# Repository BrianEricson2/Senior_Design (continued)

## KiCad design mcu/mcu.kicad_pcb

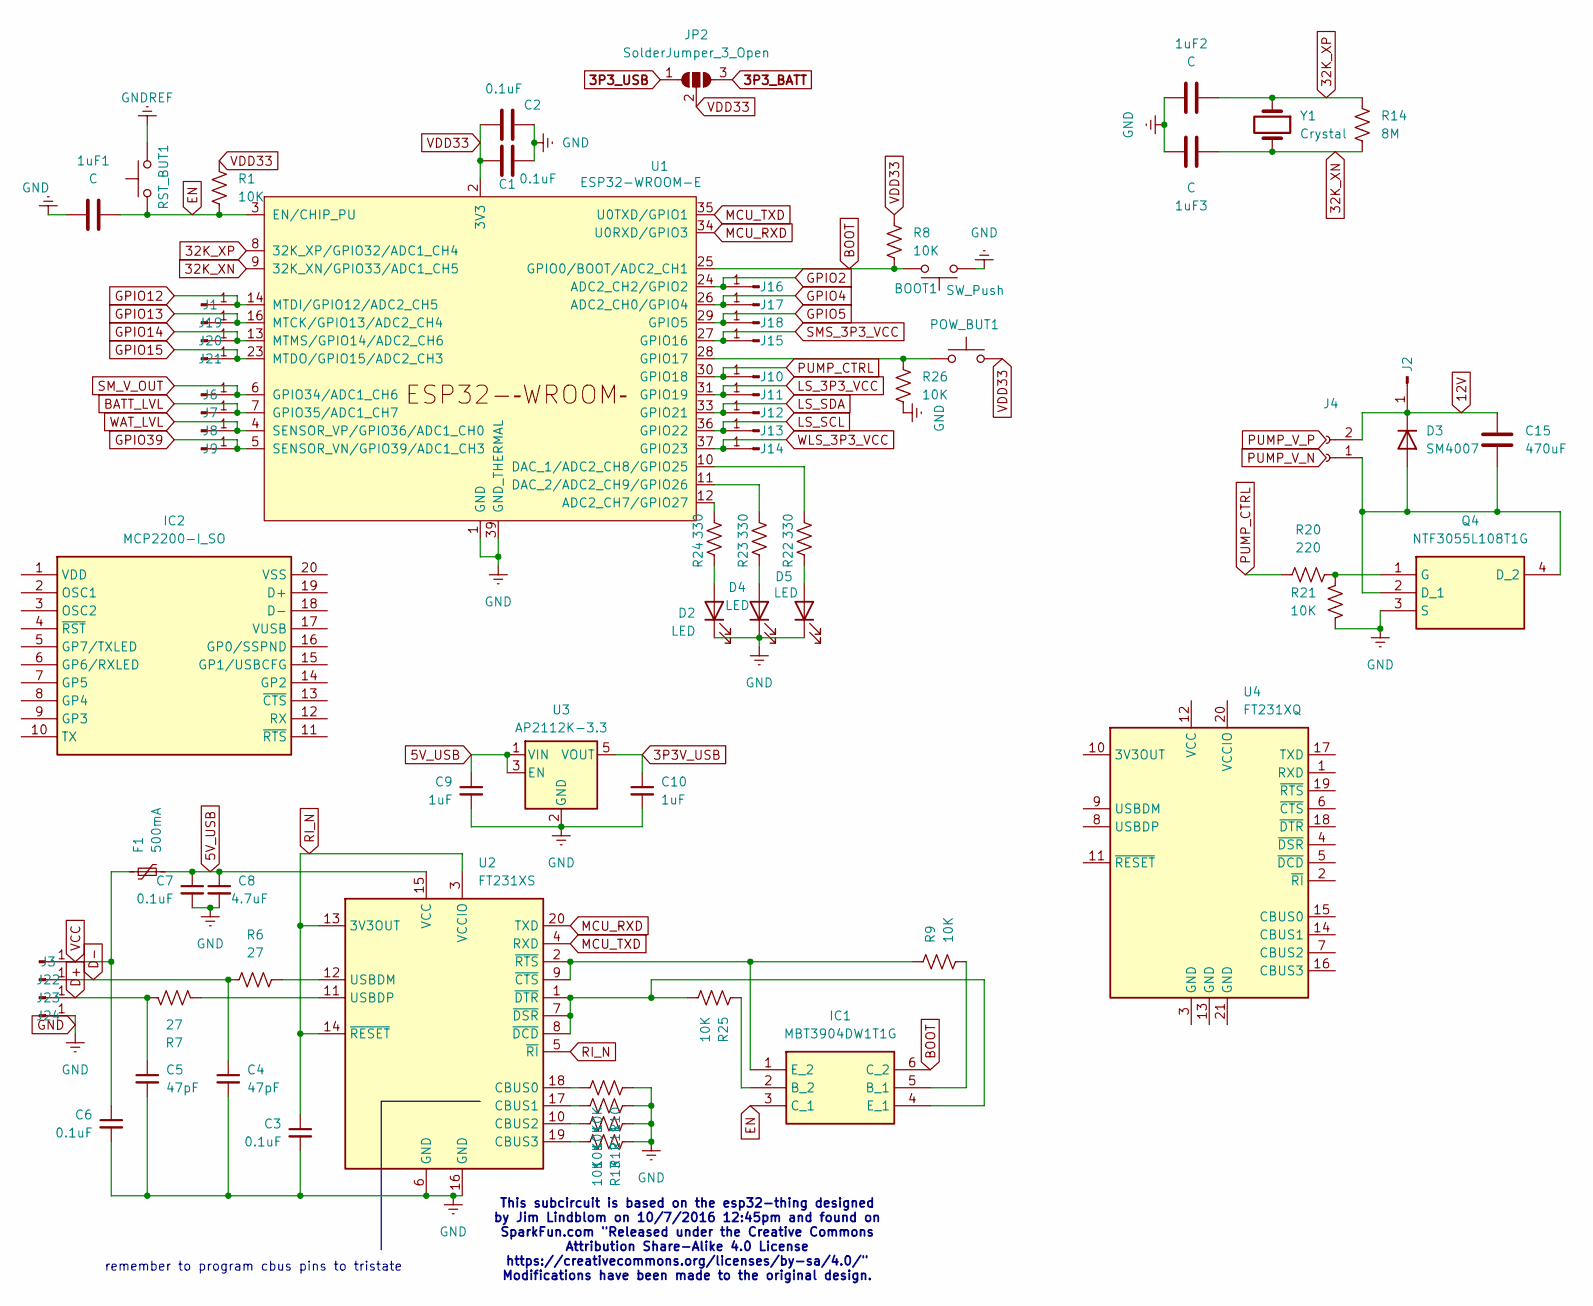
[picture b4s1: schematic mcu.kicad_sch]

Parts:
1uF1, 1uF2, 1uF3: C; C_1206_3216Metric_Pad1.33x1.80mm_HandSolder
BOOT1: SW_Push; SW_Push_SPST_NO_Alps_SKRK
C1, C2, C3, C6, C7: 0.1uF; C_1206_3216Metric_Pad1.33x1.80mm_HandSolder
C4, C5: 47pF; C_1206_3216Metric_Pad1.33x1.80mm_HandSolder
C8: 4.7uF; C_1206_3216Metric_Pad1.33x1.80mm_HandSolder
C9, C10: 1uF; C_1206_3216Metric_Pad1.33x1.80mm_HandSolder
C15: 470uF; C_1206_3216Metric_Pad1.33x1.80mm_HandSolder
D2, D4, D5: LED; LED_1206_3216Metric_Pad1.42x1.75mm_HandSolder
D3: SM4007; D_MELF
F1: 500mA; Fuse_1206_3216Metric_Pad1.42x1.75mm_HandSolder
IC1: MBT3904DW1T1G; SOT65P210X110-6N; Mouser Part Number 863-MBT3904DW1T1G
IC2: MCP2200-I_SO; SOIC127P1030X265-20N; Mouser Part Number 579-MCP2200-I/SO
J1, J2, J3, J6, J7, J8, J9, J10, J11, J12, J13, J14, J15, J16, J17, J18, J19, J20, J21, J22, J23, J24: Conn_01x01_Pin; PinHeader_1x01_P2.00mm_Vertical
J4: Conn_01x02; PinSocket_1x02_P1.00mm_Vertical_SMD_Pin1Left
JP2: SolderJumper_3_Open; SolderJumper-3_P1.3mm_Open_Pad1.0x1.5mm_NumberLabels
POW_BUT1: SW_Push; SW_Push_SPST_NO_Alps_SKRK
Q4: NTF3055L108T1G; SOT230P700X175-4N; Mouser Part Number 863-NTF3055L108T1G
R1, R8, R9, R10, R11, R12, R13, R21, R25, R26: 10K; R_1206_3216Metric_Pad1.30x1.75mm_HandSolder
R6, R7: 27; R_1206_3216Metric_Pad1.30x1.75mm_HandSolder
R14: 8M; R_1206_3216Metric_Pad1.30x1.75mm_HandSolder
R20: 220; R_1206_3216Metric_Pad1.30x1.75mm_HandSolder
R22, R23, R24: 330; R_1206_3216Metric_Pad1.30x1.75mm_HandSolder
RST_BUT1: SW_Push; SW_Push_SPST_NO_Alps_SKRK
U1: ESP32-WROOM-E; ESP32-WROOM-32E
U2: FT231XS; SSOP-20_3.9x8.7mm_P0.635mm
U3: AP2112K-3.3; SOT-23-5
U4: FT231XQ; QFN-20-1EP_4x4mm_P0.5mm_EP2.5x2.5mm
Y1: Crystal; Crystal_SMD_TXC_AX_8045-2Pin_8.0x4.5mm

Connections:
3P3V_USB: C10.1, U3.5 (VOUT)
3P3_BATT: JP2.3 (B)
3P3_USB: JP2.1 (A)
5V_USB: C7.1, C8.1, C9.1, F1.2, U2.15 (VCC), U3.1 (VIN), U3.3 (EN)
12V: C15.1, D3.1 (K), J2.1, J4.2
32K_XN: 1uF3.1, R14.2, U1.9 (32K_XN/GPIO33/ADC1_CH5), Y1.2
32K_XP: 1uF2.1, R14.1, U1.8 (32K_XP/GPIO32/ADC1_CH4), Y1.1
BATT_LVL: J7.1, U1.7 (GPIO35/ADC1_CH7)
BOOT: BOOT1.1, IC1.6 (C_2), R8.2, U1.25 (GPIO0/BOOT/ADC2_CH1)
D+: C5.1, J23.1, R7.2
D-: C4.1, J22.1, R6.2
EN: 1uF1.1, IC1.3 (C_1), R1.2, RST_BUT1.1, U1.3 (EN/CHIP_PU)
GND: 1uF1.2, 1uF2.2, 1uF3.2, BOOT1.2, C1.1, C2.1, C3.2, C4.2, C5.2, C6.2, C7.2, C8.2, C9.2, C10.2, D2.1 (K), D4.1 (K), D5.1 (K), J24.1, Q4.3 (S), R10.1, R11.1, R12.1, R13.1, R21.2, R26.2, U1.1 (GND), U1.15 (GND), U1.38 (GND), U1.39 (GND_THERMAL), U2.6 (GND), U2.16 (GND), U3.2 (GND)
GNDREF: RST_BUT1.2
GPIO2: J16.1, U1.24 (ADC2_CH2/GPIO2)
GPIO4: J17.1, U1.26 (ADC2_CH0/GPIO4)
GPIO5: J18.1, U1.29 (GPIO5)
GPIO12: J1.1, U1.14 (MTDI/GPIO12/ADC2_CH5)
GPIO13: J19.1, U1.16 (MTCK/GPIO13/ADC2_CH4)
GPIO14: J20.1, U1.13 (MTMS/GPIO14/ADC2_CH6)
GPIO15: J21.1, U1.23 (MTDO/GPIO15/ADC2_CH3)
GPIO39: J9.1, U1.5 (SENSOR_VN/GPIO39/ADC1_CH3)
LS_3P3_VCC: J11.1, U1.31 (GPIO19)
LS_SCL: J13.1, U1.36 (GPIO22)
LS_SDA: J12.1, U1.33 (GPIO21)
MCU_RXD: U1.34 (U0RXD/GPIO3), U2.20 (TXD)
MCU_TXD: U1.35 (U0TXD/GPIO1), U2.4 (RXD)
unnamed: D2.2 (A), R24.1
unnamed: C15.2, D3.2 (A), J4.1, Q4.2 (D_1), Q4.4 (D_2)
unnamed: D4.2 (A), R23.1
unnamed: D5.2 (A), R22.1
unnamed: IC1.5 (B_1), R9.2
unnamed: IC1.2 (B_2), R25.1
unnamed: IC1.4 (E_1), R25.2, U2.1 (~DTR), U2.7 (~DSR), U2.8 (~DCD)
unnamed: IC1.1 (E_2), R9.1, U2.2 (~RTS), U2.9 (~CTS)
unnamed: Q4.1 (G), R20.2, R21.1
unnamed: R24.2, U1.12 (ADC2_CH7/GPIO27)
unnamed: R22.2, U1.10 (DAC_1/ADC2_CH8/GPIO25)
unnamed: R23.2, U1.11 (DAC_2/ADC2_CH9/GPIO26)
unnamed: POW_BUT1.2, R26.1, U1.28 (GPIO17)
unnamed: R10.2, U2.18 (CBUS0)
unnamed: R11.2, U2.17 (CBUS1)
unnamed: R12.2, U2.10 (CBUS2)
unnamed: R13.2, U2.19 (CBUS3)
unnamed: R6.1, U2.12 (USBDM)
unnamed: R7.1, U2.11 (USBDP)
PUMP_CTRL: J10.1, R20.1, U1.30 (GPIO18)
RI_N: C3.1, U2.3 (VCCIO), U2.5 (~RI), U2.13 (3V3OUT), U2.14 (~RESET)
SMS_3P3_VCC: J15.1, U1.27 (GPIO16)
SM_V_OUT: J6.1, U1.6 (GPIO34/ADC1_CH6)
VCC: C6.1, F1.1, J3.1
VDD33: C1.2, C2.2, JP2.2 (C), POW_BUT1.1, R1.1, R8.1, U1.2 (3V3)
WAT_LVL: J8.1, U1.4 (SENSOR_VP/GPIO36/ADC1_CH0)
WLS_3P3_VCC: J14.1, U1.37 (GPIO23)

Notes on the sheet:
This subcircuit is based on the esp32-thing designed by Jim Lindblom on 10/7/2016 12:45pm and found on SparkFun.com "Released under the Creative Commons Attribution Share-Alike 4.0 License https://creativecommons.org/licenses/by-sa/4.0/" Modifications have been made to the original design.
remember to program cbus pins to tristate

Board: 4 copper layers, 71 parts (0 on the bottom side), 51 nets, no tracks yet.

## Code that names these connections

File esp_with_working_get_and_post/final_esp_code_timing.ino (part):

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String sampling_period_disp = "";
String watering_duration_disp = "";

const int water_lvl_pin = 36; //GPIO36 - pin 4
const int sms_data_pin = 34; //GPIO34 - pin 6
const int battery_lvl_pin = 35; //GPIO35 - pin 7
const int sms_power_pin = 16; //GPIO16 - pin 27
const int light_sensor_pwr_pin = 17; //GPIO17 - pin 28
const int pump_ctrl_pin = 18; //GPIO18 - pin 30
const int wls_power_pin = 23; //GPIO23 - pin 37
const int ledPin     = 2;    // Onboard blue LED

// use addr 0x23 if addr pin voltage is < 0.7*Vcc
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
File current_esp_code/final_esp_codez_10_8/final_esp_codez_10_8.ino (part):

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// String sampling_period_disp = "";
// String watering_duration_disp = "";

const int light_sensor_pwr_pin = 18; //GPIO18
const int pump_ctrl_pin = 16; //GPIO16
const int sms_power_pin = 19; //GPIO19
const int i2c_sda = 21; // i2c serial data = GPIO 21
const int i2c_scl = 22; // i2c serial clock = GPIO22
const int wls_power_pin = 23; //GPIO23
const int ledPin1     = 25; // pin 10 on esp32 ic
const int ledPin2     = 26; // pin 11 on esp32 ic
const int ledPin3     = 27; // pin 12 on esp32 ic
const int sms_data_pin = 32; //GPIO32
const int battery_lvl_pin = 34; //GPIO34
const int wls_signal = 35;

// use addr 0x23 if addr pin voltage is < 0.7*Vcc
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  pinMode(ledPin2, OUTPUT); digitalWrite(ledPin2, LOW);
  pinMode(ledPin3, OUTPUT); digitalWrite(ledPin3, LOW);
  //digitalWrite(wls_power_pin,LOW);
  pinMode(pump_ctrl_pin,OUTPUT); digitalWrite(pump_ctrl_pin,LOW);
  pinMode(sms_power_pin,OUTPUT); digitalWrite(sms_power_pin,LOW);
  pinMode(light_sensor_pwr_pin,OUTPUT); digitalWrite(light_sensor_pwr_pin,LOW);
  pinMode(wls_power_pin,OUTPUT); digitalWrite(wls_power_pin,LOW);
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void water_plant() {
  Serial.println("Enabling power to plant");
  unsigned long current_time = micros();
  digitalWrite(pump_ctrl_pin, HIGH);
  digitalWrite(ledPin3, HIGH);

  // (max limit - buffer) - current_time
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    unsigned long stop_counter = watering_duration_us - dist_from_limit;
    while(micros() < stop_counter) {}
  }
  digitalWrite(pump_ctrl_pin, LOW);
  digitalWrite(ledPin3, LOW);
  
  Serial.println("Disabling power to plant");
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
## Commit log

2025-06-22 Async Web Server; Est. Wifi connection
2025-07-08 Initialize soil moisture sensor data; sleep mode; timer wakeup; can not display web page while using sleep mode
2025-07-09 Create Demo
2025-07-21 peripheral codes added
2025-07-21 light sensor update
2025-07-23 Updates to demo server repo
2025-07-23 Connection test code
2025-08-16 pcb_design_files
2025-10-08 Upload modified ESP code w/ working GET and POST functionality
2025-10-30 10_30_2025
2025-11-01 display uuid in web page; use nonVolMem to erase flash data
2025-11-01 wifi reconnect after sleep issue fixed
